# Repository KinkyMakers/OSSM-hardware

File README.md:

# OSSM - Open Source Sex Machine

**Maintained by [Research and Desire](https://researchanddesire.com), supported by the community.**

[Read the documentation here.](https://docs.researchanddesire.com/ossm)

## What is OSSM?

**OSSM** (pronounced like "awesome") is a user-friendly, open-source sex machine designed for everyday use. Whether you're curious about sex machines or looking to build your own, OSSM provides a powerful, customizable solution you can assemble at home.

OSSM uses a servo-powered belt-driven linear rail, enabling quiet operation, high torque, and software-defined stroke and depth control at speeds up to 1 meter per second.

### Performance Specifications

| Specification | Standard (20V DC) | High Power (36V DC) |
|---------------|-------------------|---------------------|
| Force output  | 32 lbs (14 kg)    | 50 lbs (22 kg)      |
| Stroke length | 8" (20 cm)        | 8" (20 cm)          |
| Rail size     | 350mm             | 350mm               |

### Why Build an OSSM?

- **Full control** over stroke length, depth, and speed through software
- **Quiet operation** suitable for shared living spaces
- **Customization options** through community-developed mods
- **Learning opportunities** in mechanics, electronics, and computing

## Quick Links

| Resource | Description |
|----------|-------------|
| [Documentation](https://docs.researchanddesire.com/ossm) | Complete build guides, hardware specs, and software reference |
| [R+D Store](https://researchanddesire.com) | Purchase motors, PCBs, wire harnesses, and complete kits |
| [KinkyMakers Discord](https://discord.gg/VtZcudpxT6) | Community discussion, build help, and mod development |
| [FAQs](https://docs.researchanddesire.com/ossm/guides/housekeeping/faqs) | Common questions about hardware, motors, printing, and control |

---

## Building Your OSSM

For complete step-by-step instructions, see the [Build Guide](https://docs.researchanddesire.com/ossm/guides/getting-started/build-guide/step-0.0_introduction).

### Bill of Materials

For the complete parts list with supplier links, see [Required Tools and Parts](https://docs.researchanddesire.com/ossm/guides/getting-started/build-guide/step-1.0_required_tools_and_parts).

### Electronics

| Component | Description | Documentation |
|-----------|-------------|---------------|
| Motor | 57AIM30 "Gold Motor" | [Motor Documentation](https://docs.researchanddesire.com/ossm/Hardware/motor/standard-build-motor) |
| Reference Board | OSSM PCB or ESP32 Development Board | [Board Design](https://docs.researchanddesire.com/ossm/Hardware/PCB/board-design) |
| Remote | OSSM Wired Remote | [Remote Documentation](https://docs.researchanddesire.com/ossm/Hardware/standard-printed-parts/remote/introduction) |
| Wiring | JST-PH 2.0 4-Pin data cable and 16awg power wire | [Wiring Guide](https://docs.researchanddesire.com/ossm/Hardware/motor/wiring-gold-motor) |

**Power Supply:** 20-36V DC (5.5 x 2.1 Barrel Plug). A 24V 5A supply is recommended. Higher voltage (up to 36V) provides increased force.

> **Portable Option:** USB Power Banks capable of true 100W USB PD generally work well.
> - INIU Power Bank P63-E1 100W (tested, works)
> - INIU B62 Power Bank 65W (tested, powers down on high load)

### Printed Parts

For 3D printing settings and material recommendations, see [3D Printing Parts](https://docs.researchanddesire.com/ossm/guides/getting-started/build-guide/step-1.2_3d-printing-parts).

| Assembly | Parts Included | Documentation |
|----------|----------------|---------------|
| [Actuator](Printed%20Parts/Actuator/) | Body, Belt Tensioner, Threaded End Effector | [Actuator Docs](https://docs.researchanddesire.com/ossm/Hardware/standard-printed-parts/actuator/introduction) |
| [Remote](Printed%20Parts/Remote/) | Body, Knobs, Top Cover | [Remote Docs](https://docs.researchanddesire.com/ossm/Hardware/standard-printed-parts/remote/introduction) |
| [Toy Mounting](Printed%20Parts/Toy%20Mounting/) | Flange Base, Vac-U-Lock Adapters | [Toy Mounting Docs](https://docs.researchanddesire.com/ossm/Hardware/standard-printed-parts/toy-mounting/introduction) |
| [Mounting](Printed%20Parts/Mounting/) | PitClamp Mini Ring/Base, PCB Enclosure | [Mounting Docs](https://docs.researchanddesire.com/ossm/Hardware/standard-printed-parts/pitclamp/README) |
| [Stand](Printed%20Parts/Stand/) | 3030 Extrusion Base Components | [Stand Docs](https://docs.researchanddesire.com/ossm/Hardware/standard-printed-parts/stand/introduction) |
| [Radiating PitClamp Stand](Printed%20Parts/OSSM%20Mods/Radiating%20PitClamp%20Stand/) | One- and two-arm kits with a captured handle and four-color artwork | [Kit files and notes](Printed%20Parts/OSSM%20Mods/Radiating%20PitClamp%20Stand/README.md) |

Experimental parts are developed in the [KinkyMakers Discord](https://discord.gg/wrENMKb3) `#ossm-print-testing` channel.

### Hardware Components

**GT2 Pulley**
- Qty 1: 8mm Bore, 20 Tooth, 10mm Width

**GT2 Timing Belt**
- Qty 1: 10mm Width, 500mm length

**MGN12H Rail + Bearing Block**
- Qty 1: Minimum 250mm, Suggested 350mm, Maximum 550mm
- Rail length = desired maximum stroke + 180mm
- Must be MGN**12H** (H = longer bearing block for stability, 12 = 12mm rail width)

**Ball Bearings**
- Qty 6: MR115-2RS 5x11x4mm

**Fasteners**
| Qty | Part |
|-----|------|
| 8 | M3x8 Socket Cap Head Bolt |
| 2 | M3x16 Socket Cap Head Bolt |
| 1 | M3x20 Socket Cap Head Bolt |
| 7 | M3 Hex Nut |
| 3 | M5x20 Socket Cap Head Bolt |
| 1 | M5 Hex Nut |
| 4 | M5x35 Socket Cap Head Bolt |
| 4 | M5 20mm Hex Coupling Nut (or M5 Hex Nut) |

Additional hardware is required for Stand, Mounting, and Remote assemblies. See the respective [Printed Parts](Printed%20Parts/) folders for details.

---

## Assembly

**Important:** The actuator rail direction is critical for pattern accuracy and safety. The proper orientation has the threaded end to the right when looking at the front face of the actuator body (the "M" side of the OSSM text on the cover).

Your rail should extend the threaded end first when booted. If this doesn't match your build's behavior, reverse your rail's printed hardware.

### Build Resources

| Resource | Description |
|----------|-------------|
| [Complete Build Guide](https://docs.researchanddesire.com/ossm/guides/getting-started/build-guide/step-0.0_introduction) | Step-by-step documentation with images |
| [OSSM Assembly Playlist](https://youtube.com/playlist?list=PLzSK7OAu3KNQsFo6WJGT8P28lfkD3xpps) | Video tutorials for each assembly step |
| [Complete Assembly - Follow Along Guide](https://www.youtube.com/watch?v=9lVobSEw_Uw) | Full 30-minute video walkthrough |

---

## Software

For firmware flashing and configuration, see the [Software Documentation](https://docs.researchanddesire.com/ossm/Software/getting-started/introduction).

| Resource | Description |
|----------|-------------|
| [Web Flasher](https://docs.researchanddesire.com/ossm/guides/getting-started/web-flasher) | Flash firmware directly from your browser |
| [PlatformIO Setup](https://docs.researchanddesire.com/ossm/Software/getting-started/PlatformIO) | Development environment for custom builds |
| [LED Status Guide](https://docs.researchanddesire.com/ossm/Software/getting-started/LED_Status) | Understanding indicator lights |
| [StrokeEngine](https://docs.researchanddesire.com/ossm/Software/motion/stroke-engine/introduction) | Motion control library documentation |
| [Hardware Tests](https://docs.researchanddesire.com/ossm/Software/getting-started/hardware-tests) | On-device test suites for verifying peripherals, BLE, WiFi, and homing |

---

## Getting Help

- [User Guide](https://docs.researchanddesire.com/ossm/guides/getting-started/user-guide/introduction) - Operating your OSSM
- [Troubleshooting](https://docs.researchanddesire.com/ossm/guides/getting-started/user-guide/troubleshooting) - Common issues and solutions
- [Safety Information](https://docs.researchanddesire.com/ossm/guides/housekeeping/safety/introduction) - Important safety guidance
- [Discord Community](https://discord.gg/VtZcudpxT6) - Real-time community support

---

## Contributing

OSSM is open-source hardware under the [CERN Open Hardware Licence Version 2 - Strongly Reciprocal](LICENSE).

- [How to Become a Contributor](https://docs.researchanddesire.com/ossm/guides/contributing/how-to-become-a-contributor)
- [Forking the Repository](https://docs.researchanddesire.com/ossm/guides/contributing/forking)
- [Reporting Issues](https://docs.researchanddesire.com/ossm/guides/contributing/reporting-issues)
- [Roadmap](https://docs.researchanddesire.com/ossm/guides/contributing/roadmap)

---

## About

- [About Research and Desire](https://docs.researchanddesire.com/ossm/guides/housekeeping/about-research-and-desire)
- [About Kinky Makers](https://docs.researchanddesire.com/ossm/guides/housekeeping/about-kinky-makers)
- [Open Source Certification](https://docs.researchanddesire.com/ossm/guides/housekeeping/open-source/introduction)

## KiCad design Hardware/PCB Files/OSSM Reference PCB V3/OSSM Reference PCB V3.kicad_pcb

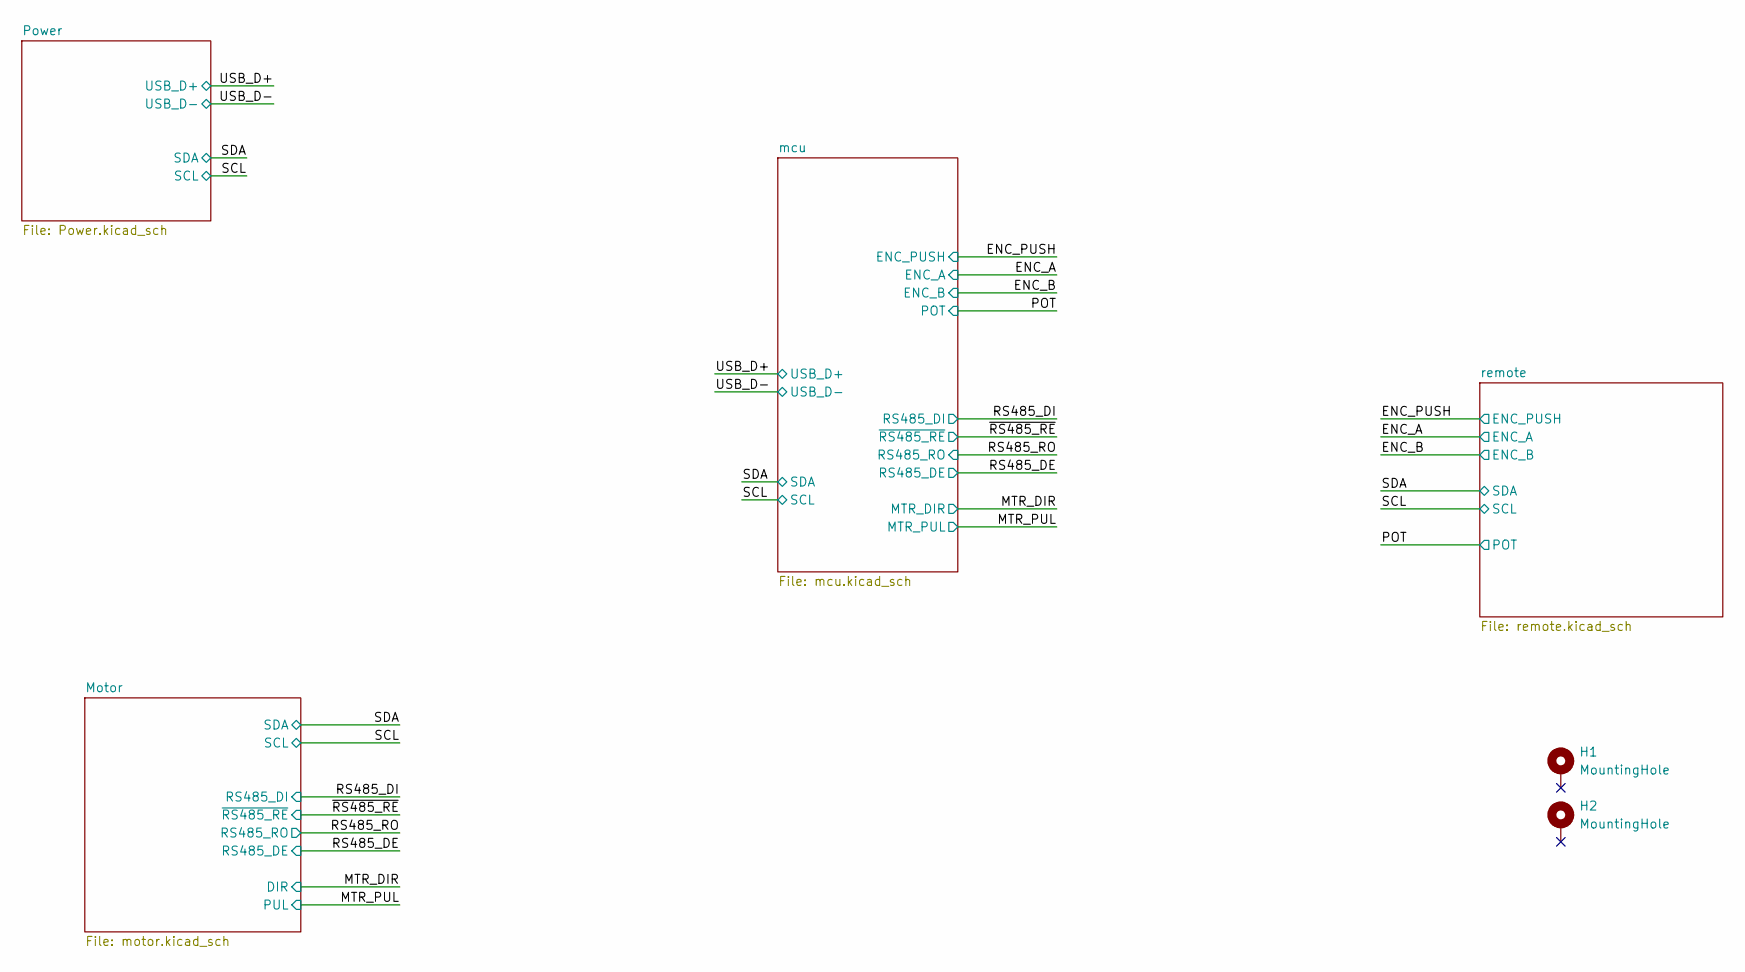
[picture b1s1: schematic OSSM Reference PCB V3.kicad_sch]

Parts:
H1, H2: MountingHole; MountingHole_4.3mm_M4_DIN965_Pad

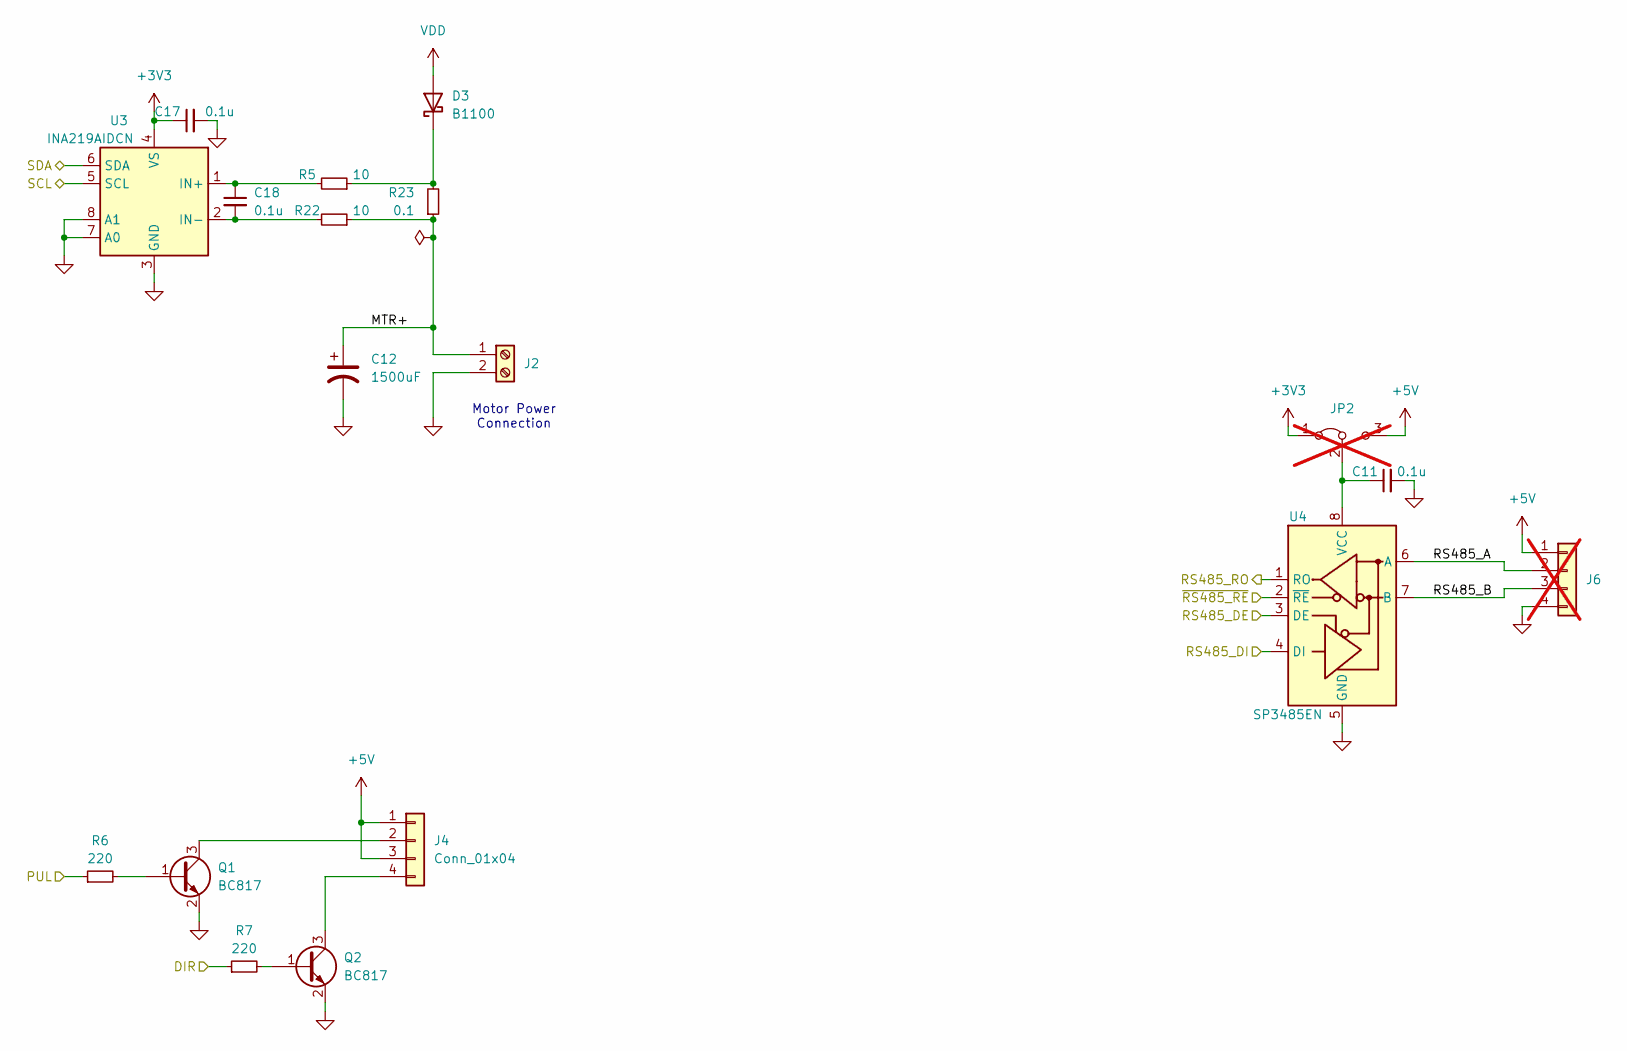
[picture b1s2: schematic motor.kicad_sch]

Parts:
C11: 0.1u; C_0402_1005Metric; MPN C77020
C12: 1500uF; CP_Radial_D12.5mm_P5.00mm_L25mm; MPN C2832301
C17, C18: 0.1u; C_0402_1005Metric; MPN C56392
D3: B1100; D_SMA; MPN C110106
J2: Screw_Terminal_01x02; TerminalBlock_Phoenix_MKDS-1,5-2_1x02_P5.00mm_Horizontal; MPN C8269
J4: Conn_01x04; Molex_Micro-Fit_3.0_43650-0400_1x04_P3.00mm_Horizontal
J6: Conn_01x04; PinSocket_1x04_P2.54mm_Vertical; not fitted
JP2: Jumper_3_Bridged12; SolderJumper-3_P1.3mm_Bridged12_Pad1.0x1.5mm; not fitted
Q1, Q2: BC817; SOT-23; MPN C52801
R5, R22: 10; R_0402_1005Metric
R6, R7: 220; R_0402_1005Metric
R23: 0.1; R_0603_1608Metric; MPN C111027
U3: INA219AIDCN; SOT-23-8; MPN C87469
U4: SP3485EN; SOIC-8_3.9x4.9mm_P1.27mm; MPN C8963

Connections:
+3V3: C17.1, JP2.1 (A), U3.4 (VS); also elsewhere on the board
+5V: J4.1, J4.3, J6.1, JP2.3 (B); also elsewhere on the board
/MTR_DIR: R7.1; also elsewhere on the board
/MTR_PUL: R6.1; also elsewhere on the board
/Motor/MTR+: C12.1, J2.1, R22.1, R23.1
/Motor/RS485_A: J6.2, U4.6 (A)
/Motor/RS485_B: J6.3, U4.7 (B)
/RS485_DE: U4.3 (DE); also elsewhere on the board
/RS485_DI: U4.4 (DI); also elsewhere on the board
/RS485_RO: U4.1 (RO); also elsewhere on the board
/SCL: U3.5 (SCL); also elsewhere on the board
/SDA: U3.6 (SDA); also elsewhere on the board
/~RS485_RE: U4.2 (~RE); also elsewhere on the board
GND: C11.2, C12.2, C17.2, J2.2, J6.4, Q1.2 (E), Q2.2 (E), U3.3 (GND), U3.7 (A0), U3.8 (A1), U4.5 (GND); also elsewhere on the board
unnamed: D3.1 (K), R5.1, R23.2
unnamed: J4.2, Q1.3 (C)
unnamed: J4.4, Q2.3 (C)
unnamed: C11.1, JP2.2 (C), U4.8 (VCC)
unnamed: Q1.1 (B), R6.2
unnamed: Q2.1 (B), R7.2
unnamed: C18.1, R5.2, U3.1 (IN+)
unnamed: C18.2, R22.2, U3.2 (IN-)
VDD: D3.2 (A); also elsewhere on the board

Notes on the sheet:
Motor Power Connection

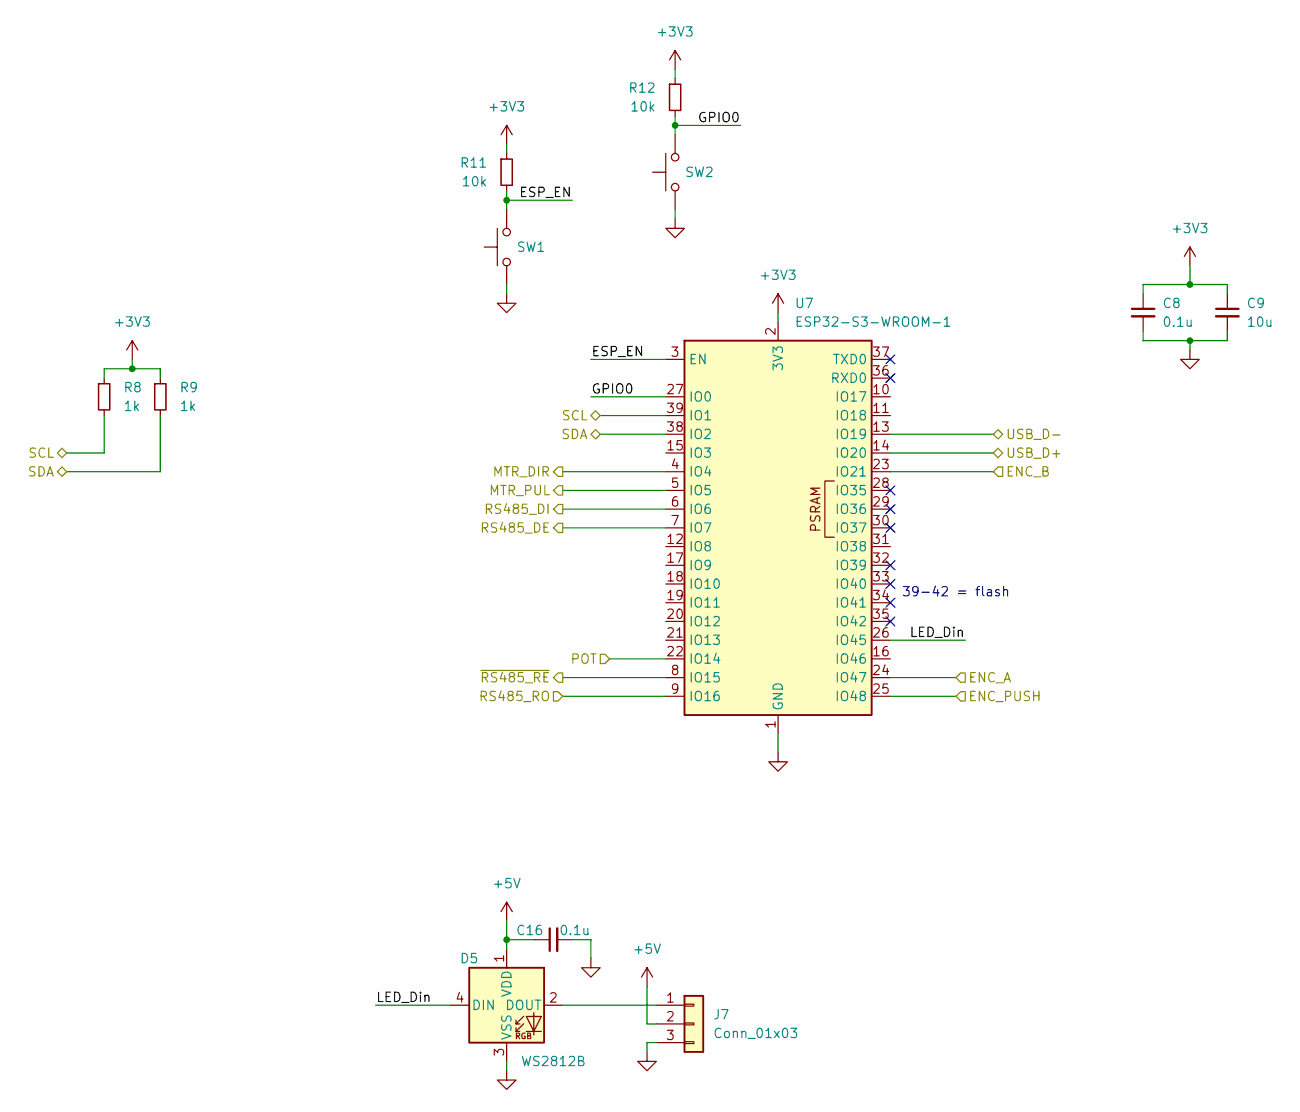
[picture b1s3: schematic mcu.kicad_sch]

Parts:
C8, C16: 0.1u; C_0402_1005Metric; MPN C77020
C9: 10u; C_0603_1608Metric; MPN C194427
D5: WS2812B; LED_WS2812B_PLCC4_5.0x5.0mm_P3.2mm; MPN C2843785
J7: Conn_01x03; PinHeader_1x03_P2.54mm_Vertical
R8, R9: 1k; R_0402_1005Metric
R11, R12: 10k; R_0402_1005Metric
SW1, SW2: SW_Push; SW_TACT_TS-1088-AR02016; MPN C720477
U7: ESP32-S3-WROOM-1; MPN C2913199

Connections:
+3V3: C8.1, C9.1, R8.1, R9.1, R11.1, R12.1, U7.2 (3V3); also elsewhere on the board
+5V: C16.1, D5.1 (VDD), J7.2; also elsewhere on the board
/ENC_A: U7.24 (IO47); also elsewhere on the board
/ENC_B: U7.23 (IO21); also elsewhere on the board
/ENC_PUSH: U7.25 (IO48); also elsewhere on the board
/MTR_DIR: U7.4 (IO4); also elsewhere on the board
/MTR_PUL: U7.5 (IO5); also elsewhere on the board
/POT: U7.22 (IO14); also elsewhere on the board
/RS485_DE: U7.7 (IO7); also elsewhere on the board
/RS485_DI: U7.6 (IO6); also elsewhere on the board
/RS485_RO: U7.9 (IO16); also elsewhere on the board
/SCL: R8.2, U7.39 (IO1); also elsewhere on the board
/SDA: R9.2, U7.38 (IO2); also elsewhere on the board
/USB_D+: U7.14 (IO20); also elsewhere on the board
/USB_D-: U7.13 (IO19); also elsewhere on the board
/mcu/ESP_EN: R11.2, SW1.2, U7.3 (EN)
/mcu/GPIO0: R12.2, SW2.2, U7.27 (IO0)
/mcu/LED_Din: D5.4 (DIN), U7.26 (IO45)
/~RS485_RE: U7.8 (IO15); also elsewhere on the board
GND: C8.2, C9.2, C16.2, D5.3 (VSS), J7.3, SW1.1, SW2.1, U7.1 (GND), U7.40 (GND), U7.41 (GND); also elsewhere on the board
unnamed: D5.2 (DOUT), J7.1

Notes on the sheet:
39-42 = flash

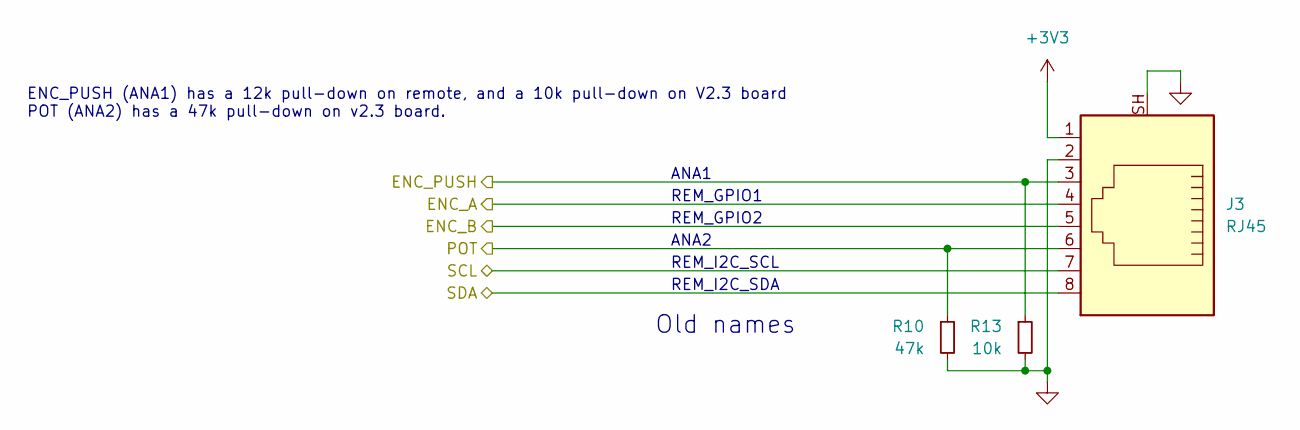
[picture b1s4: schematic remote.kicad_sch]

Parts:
J3: RJ45; RJ45_Connfly_DS1128-09-S8xx-S_Horizontal; MPN C86575
R10: 47k; R_0402_1005Metric
R13: 10k; R_0402_1005Metric

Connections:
+3V3: J3.1; also elsewhere on the board
/ENC_A: J3.4; also elsewhere on the board
/ENC_B: J3.5; also elsewhere on the board
/ENC_PUSH: J3.3, R13.1; also elsewhere on the board
/POT: J3.6, R10.1; also elsewhere on the board
/SCL: J3.7; also elsewhere on the board
/SDA: J3.8; also elsewhere on the board
GND: J3.2, J3.SH, R10.2, R13.2; also elsewhere on the board

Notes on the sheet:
ANA2
REM_I2C_SCL
REM_GPIO2
ANA1
ENC_PUSH (ANA1) has a 12k pull-down on remote, and a 10k pull-down on V2.3 board POT (ANA2) has a 47k pull-down on v2.3 board.
Old names
REM_I2C_SDA
REM_GPIO1

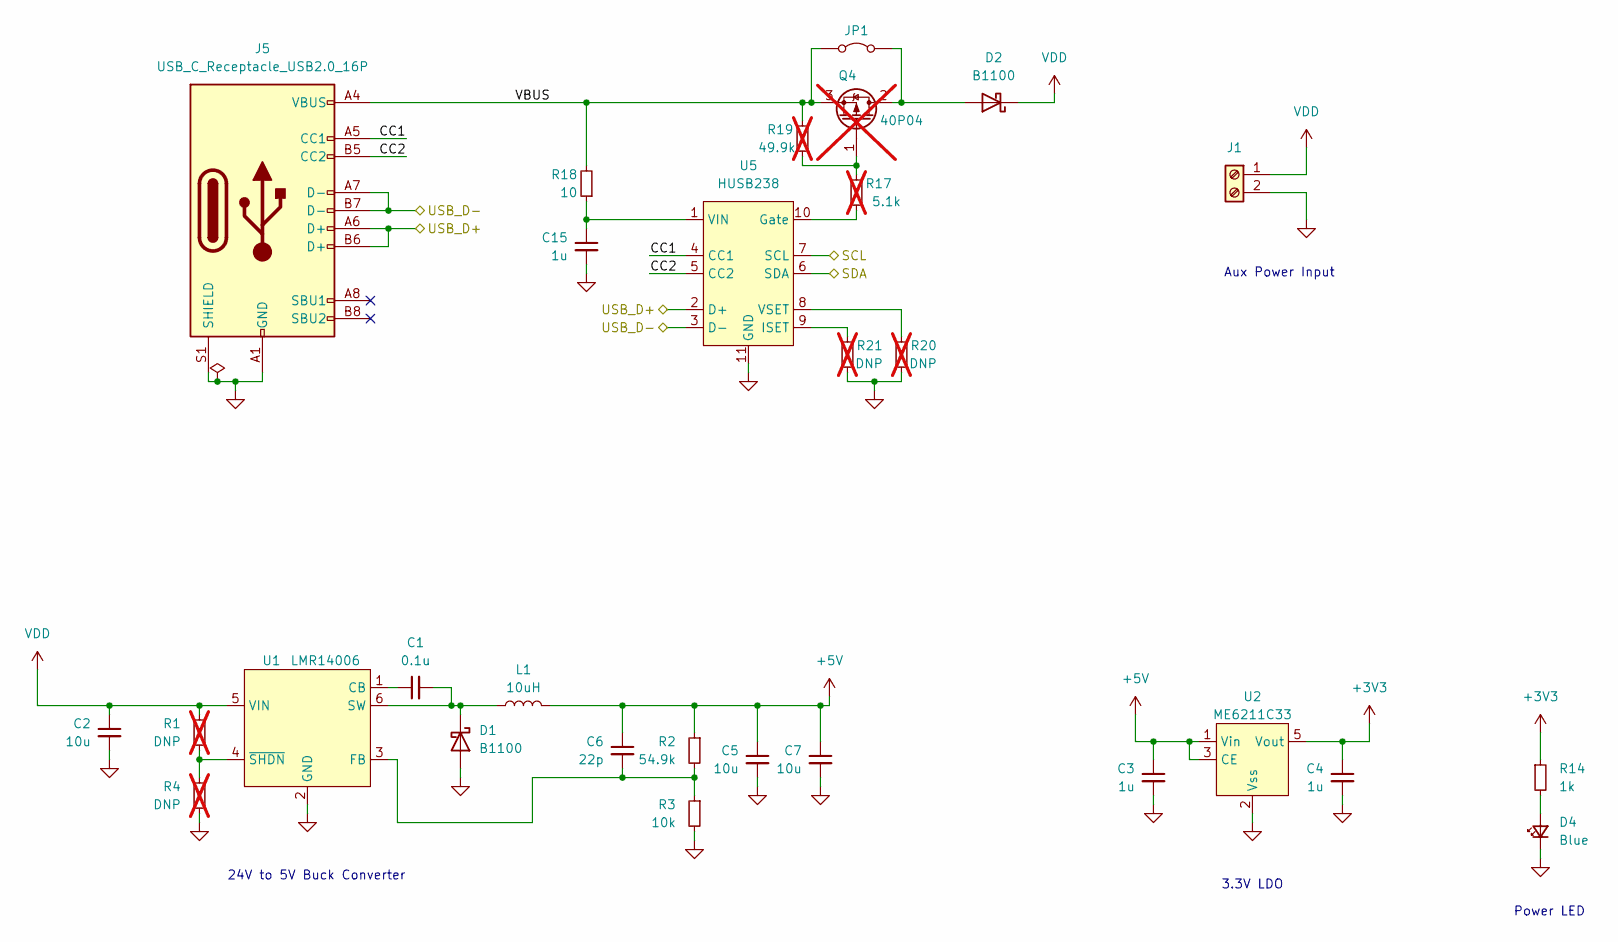
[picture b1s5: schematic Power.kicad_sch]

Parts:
C1: 0.1u; C_0402_1005Metric; MPN C77020
C2, C5, C7: 10u; C_0603_1608Metric; MPN C194427
C3, C4, C15: 1u; C_0402_1005Metric; MPN C1518208
C6: 22p; C_0402_1005Metric; MPN C76960
D1, D2: B1100; D_SMA; MPN C110106
D4: Blue; LED_0603_1608Metric; MPN C7496819
J1: Screw_Terminal_01x02; TerminalBlock_Phoenix_MKDS-1,5-2_1x02_P5.00mm_Horizontal; MPN C8269
J5: USB_C_Receptacle_USB2.0_16P; USB_C_Receptacle_HRO_TYPE-C-31-M-12; MPN C165948
JP1: Jumper_2_Bridged; SolderJumper-2_P1.3mm_Bridged_Pad1.0x1.5mm
L1: 10uH; L_Sunlord_SWPA4020S; MPN C98364
Q4: 40P04; TO-252-2; MPN C21882500; not fitted
R1, R4, R20, R21: DNP; R_0402_1005Metric; not fitted
R2: 54.9k; R_0402_1005Metric
R3: 10k; R_0402_1005Metric
R14: 1k; R_0402_1005Metric
R17: 5.1k; R_0402_1005Metric; MPN C278598; not fitted
R18: 10; R_0402_1005Metric
R19: 49.9k; R_0402_1005Metric; not fitted
U1: LMR14006; SOT-23-6; MPN C477919
U2: ME6211C33; SOT-23-5; MPN C82942
U5: HUSB238; DFN-10-1EP_3x3mm_P0.5mm_EP1.65x2.38mm_ThermalVias; MPN C7471904

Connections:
+3V3: C4.1, R14.1, U2.5 (Vout); also elsewhere on the board
+5V: C3.1, C5.1, C6.1, C7.1, L1.2, R2.1, U2.1 (Vin), U2.3 (CE); also elsewhere on the board
/Power/CC1: J5.A5 (CC1), U5.4 (CC1)
/Power/CC2: J5.B5 (CC2), U5.5 (CC2)
/Power/VBUS: J5.A4 (VBUS), J5.A9 (VBUS), J5.B4 (VBUS), J5.B9 (VBUS), JP1.1 (A), Q4.3 (S), R18.2, R19.2
/SCL: U5.7 (SCL); also elsewhere on the board
/SDA: U5.6 (SDA); also elsewhere on the board
/USB_D+: J5.A6 (D+), J5.B6 (D+), U5.2 (D+); also elsewhere on the board
/USB_D-: J5.A7 (D-), J5.B7 (D-), U5.3 (D-); also elsewhere on the board
GND: C2.2, C3.2, C4.2, C5.2, C7.2, C15.2, D1.2 (A), D4.1 (K), J1.2, J5.A1 (GND), J5.A12 (GND), J5.B1 (GND), J5.B12 (GND), J5.S1 (SHIELD), R3.2, R4.2, R20.1, R21.1, U1.2 (GND), U2.2 (Vss), U5.11 (GND); also elsewhere on the board
unnamed: C1.2, D1.1 (K), L1.1, U1.6 (SW)
unnamed: D2.2 (A), JP1.2 (B), Q4.2 (D)
unnamed: D4.2 (A), R14.2
unnamed: Q4.1 (G), R17.2, R19.1
unnamed: C1.1, U1.1 (CB)
unnamed: C6.2, R2.2, R3.1, U1.3 (FB)
unnamed: R1.2, R4.1, U1.4 (~SHDN)
unnamed: R17.1, U5.10 (Gate)
unnamed: R21.2, U5.9 (ISET)
unnamed: C15.1, R18.1, U5.1 (VIN)
unnamed: R20.2, U5.8 (VSET)
VDD: C2.1, D2.1 (K), J1.1, R1.1, U1.5 (VIN); also elsewhere on the board

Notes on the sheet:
Power LED
Aux Power Input
3.3V LDO
24V to 5V Buck Converter

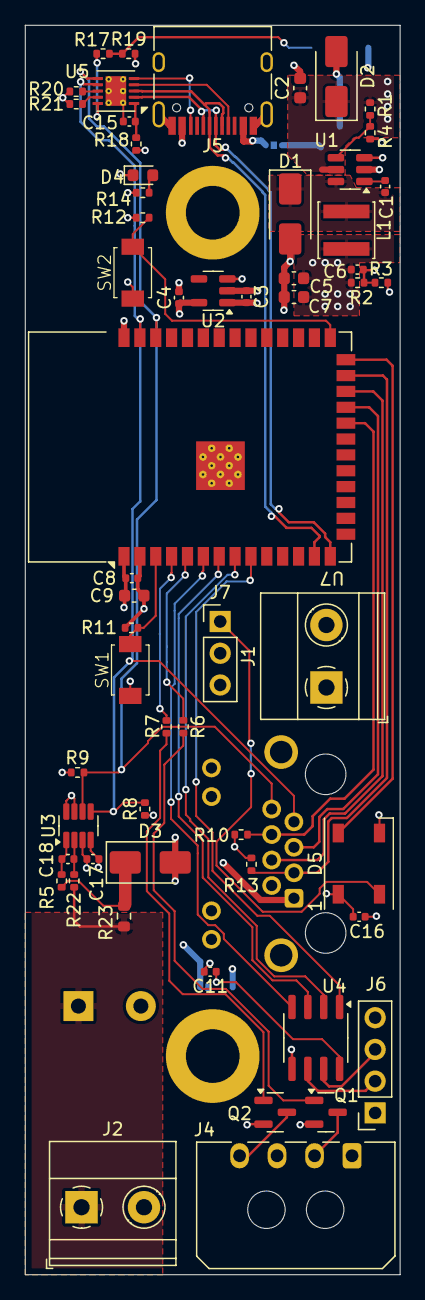
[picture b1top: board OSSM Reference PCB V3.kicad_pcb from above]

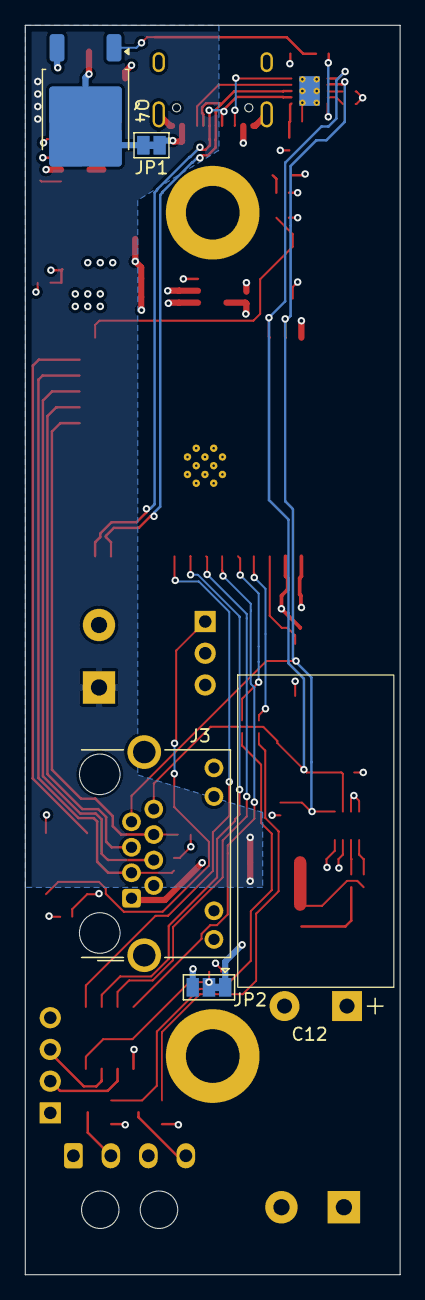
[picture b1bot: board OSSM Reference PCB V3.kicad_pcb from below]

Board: 4 copper layers, 30.0 x 100.0 mm, 64 parts (5 on the bottom side), 47 nets.

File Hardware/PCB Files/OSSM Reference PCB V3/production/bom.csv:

Designator,Footprint,Quantity,Value,LCSC Part #
"C1, C11, C16, C17, C18, C8",0402,6,0.1u,C56392
C12,CP_Radial_D12.5mm_P5.00mm_L25mm,1,1500uF,C2832301
"C15, C3, C4",0402,3,1u,C1518208
"C2, C5, C7, C9",0603,4,10u,C194427
C6,0402,1,22p,C76960
"D1, D2, D3",D_SMA,3,B1100,C110106
D4,0603,1,Blue,C7496819
D5,LED_WS2812B_PLCC4_5.0x5.0mm_P3.2mm,1,WS2812B,C2843785
"J1, J2","TerminalBlock_Phoenix_MKDS-1,5-2_1x02_P5.00mm_Horizontal",2,Screw_Terminal_01x02,C8269
J3,RJ45_Connfly_DS1128-09-S8xx-S_Horizontal,1,RJ45,C86575
J5,USB_C_Receptacle_HRO_TYPE-C-31-M-12,1,USB_C_Receptacle_USB2.0_16P,C165948
L1,L_Sunlord_SWPA4020S,1,10uH,C98364
"Q1, Q2",SOT-23,2,BC817,C52801
R10,0402,1,47k,C25792
"R11, R12, R13, R3",0402,4,10k,C60490
"R14, R8, R9",0402,3,1k,C11702
"R18, R22, R5",0402,3,10,C25077
R2,0402,1,54.9k,C5126159
R23,0603,1,0.1,C111027
"R6, R7",0402,2,220,C112291
"SW1, SW2",SW_TACT_TS-1088-AR02016,2,SW_Push,C720477
U1,SOT-23-6,1,LMR14006,C477919
U2,SOT-23-5,1,ME6211C33,C82942
U3,SOT-23-8,1,INA219AIDCN,C87469
U4,SOIC-8_3.9x4.9mm_P1.27mm,1,SP3485EN,C8963
U5,DFN-10-1EP_3x3mm_P0.5mm_EP1.65x2.38mm_ThermalVias,1,HUSB238,C7471904
U7,ESP32-S3-WROOM-1,1,ESP32-S3-WROOM-1,C2913199

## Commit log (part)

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2026-02-24 Temporary patch
2026-02-24 docs: sync ossm documentation from docs repo
2026-02-25 Go to point pattern for stroke engine.
2026-02-25 Same issue... any motion is spamming nimble updates to connected devices.
2026-02-25 Add detail to MQTT payload
2026-02-25 Consolidated streaming code updates
2026-02-25 Better default buffer
2026-02-27 Reset queue when launching streaming mode
2026-02-28 Faster homing, with userconfig for where the device should park afterwards.
2026-03-01 4x Current, but 4x faster
2026-03-02 Fix MQTT local sync
2026-03-02 Fix - does connect
2026-03-02 Fix and fingerprint
2026-03-02 Unneeded movement with new homing code
2026-03-02 Latency Characteristic
2026-03-03 docs: migrate SaladDressing mod content to documentation site
    - Add motor-cover.mdx and dp-attachment.mdx pages with hero images
    - Enrich capstan.mdx with MGN12H vs HG20 comparison, tabbed BOMs,
    inline fastener lists, assembly guide links, and full CAD file links
    - Add "Printed parts and CAD files" sections with GitHub links to all
    STEP/3MF/STL files across suction-cup-bracket, weight-plate, and
    quick-change-toy-mount pages
2026-03-03 docs: migrate legacy JPGs to webp and remove source Pictures/ directories
    - Convert additional detail/angle photos to webp and co-locate in docs _images/
    - dp-attachment-top.webp (bracket top-down view)
    - motor-cover-rear.webp, motor-cover-back.webp (heatsink angles)
    - capstan-hg20-front.webp, capstan-hg20-side.webp (HG20 overview shots)
    - Add new images to motor-cover, dp-attachment, and capstan MDX pages
    - Delete all 54 legacy JPGs from Printed Parts Pictures/ directories
2026-03-03 fix imports
2026-03-03 restore mermaid controls
2026-03-03 Simplify Docs and add MakerWorld Links
2026-03-03 Restore some material tips
2026-03-03 Remove react import
2026-03-03 Characteristic doc
2026-03-04 Basic CSV support
2026-03-04 spacing
2026-03-06 WIP commit
2026-03-09 documentation and critical bug fix
2026-03-09 removed power saving since the OSSM does not run on battery and it was causing the OSSM setup connection to fail
2026-03-09 --no-docs Simple bug fix, no UI changes
2026-03-09 String compare
2026-03-10 Display Tests
2026-03-10 Add display documentation section with UI library docs
    Move display service docs to a dedicated Display section and add
    documentation for the lib/ui rendering library covering TextPages,
    strings, icons, logos, and visual test infrastructure.
    Made-with: Cursor
2026-03-10 temp
2026-03-10 AUTO: Version bump 1.0.12
2026-03-10 Added is-paired polling to the backend so that the screen confirms the successful pairing after the user enters the pairing code on the UI
2026-03-11 AUTO: Version bump 1.0.13
2026-03-11 AUTO: Version bump 1.0.14
2026-03-11 RAD-1957
2026-03-11 Fix MQTT connection and icons
2026-03-11 shortened the URL to make the qr code work (less characters)
2026-03-11 fix icons
2026-03-11 Added pairing loading screen so the UI doesn't seem to freeze
2026-03-11 Added return text + consolidated all the pages to TextPages file (minor refactor)
2026-03-11 payload tests
2026-03-11 Commented out the polling code
2026-03-11 AUTO: Version bump 1.0.15
2026-03-14 Pattern page fix
2026-03-14 Fix and move link
2026-03-16 Reverse setting bug fix
2026-03-16 AUTO: Version bump 1.0.16
2026-03-16 Buffer state and loop
2026-03-16 Not depth
2026-03-20 initial hw test setup
2026-03-23 UPdated the tests to reuse code and not write it's own hardware control functions
2026-03-23 Updated the platformio.ini file to enable the newly added tests
2026-03-23 Undoing wronfgul update to the .ini file
2026-03-23 Added developer documentation
2026-03-23 Minor update to the readme.md to link to the new test pae
2026-03-23 Add go:restart and go:update BLE commands to OSSM firmware
2026-03-23 Fix hardware test homing slamming into hard stops by suppressing verbose GPIO logs
    Without esp_log_level_set(gpio, ESP_LOG_WARN), the ESP-IDF GPIO/ADC
    drivers emit debug logs on every analogRead() call during the homing
    current-sensing loop. Each log blocks on Serial output, starving the
    loop and delaying stall detection — causing the motor to grind against
    the hard stops for hundreds of milliseconds before stopping.
    Production (main.cpp) already suppresses these logs. Adding the same
2026-03-24 AUTO: Version bump 1.0.17
2026-03-24 AUTO: Version bump 1.0.18
2026-03-24 ALl unit tests now pass
2026-03-25 AUTO: Version bump 1.0.19
2026-03-25 Phase 2 cont.: updating simple penetration to work with the radr
2026-03-26 Phase 3.2.0: Aded eFuse MAX hex fielf to BLE pairing charactarestic value, backward-compatible
2026-03-30 Undoing accidental git commit
2026-03-30 AUTO: Version bump 1.0.20
2026-03-30 Remove build artifacts and broken submodule from main
    Removes files that were accidentally included in PR #262:
    - Software/components/esp_littlefs (submodule ref with no .gitmodules)
    - Software/dependencies.lock
    - Software/sdkconfig.development
    - Reverts compile_commands.json to pre-merge state
    The esp_littlefs submodule reference was causing CI checkout failures.
2026-03-30 AUTO: Version bump 1.0.21
2026-03-30 Release workflow
2026-03-30 AUTO: Version bump 1.0.22
2026-03-30 AUTO: Version bump 1.0.23
2026-04-01 AUTO: Version bump 1.0.24
2026-04-02 Added Picatinny Rail Mod under /Printed Parts/OSSM Mods/LaikaTheHuskie's Mods
2026-04-04 Early draft of pattern control
2026-04-08 Create OSSM Universal Toy Mounting
    Universal Mounting structure for mounting toys to the OSSM
2026-04-09 Uploaded Work in progress mounting plates and attachments
2026-04-09 Added New Plates,
2026-04-11 Added some hardware, removed some redundant parts
2026-04-11 added gridfinity nut and bolt holders
2026-04-11 Fixed some errors in plates and added missing holes in in a backplate that was missing it
2026-04-13 multiplate WIP added
2026-04-19 Before installing library
2026-04-19 Ok.. we're using spline.h
2026-04-26 Before trying acceleration control
2026-04-27 feat(funscript-player): add built-in example funscript loader (RAD-1897)
    Adds a button under the funscript file picker that loads a short, built-in
    example funscript (slow -> medium -> fast strokes) so new users can test
    the player and verify their OSSM is responding correctly without first
    needing to source a script from elsewhere.
    Linear: https://linear.app/researchanddesire/issue/RAD-1897
2026-04-27 fix(funscript-player): address RAD-2053 safety + UX issues
    Improve the OSSM funscript player to fix three of the four problems
    reported in RAD-2053:
    1. Android video picker (Issue 1): drop accept="video/*" so the
    system picker opens the full file browser instead of forcing the
    user into the Photos / Gallery app, which hid files on network
    drives.
2026-04-28 fix(funscript-player): hold reverse/simple in refs to defeat stale closure (RAD-1993)
    The Funscript Player runs a setInterval at 2ms that captured a stale
    React closure of `syncFunscript`. After toggling Reverse (or rapid
    play/pause around it), the running interval could keep emitting
    non-reversed positions for ~1-2 seconds before "fixing itself".
    This switches `isReverse` and `isSimple` to ref-mirrored values so
    each sync tick reads the current toggle. The setInterval is also
2026-04-29 Feature to rename OSSM
2026-04-29 Shorter name
2026-04-30 8 Characters
2026-04-30 Even better homing
2026-04-30 Double tap all instrokes
2026-04-30 Only bump twice if stroke is short
2026-04-30 Pin to 2.4 as 2.5 is currently incompatible
2026-04-30 Incorrect test result
2026-05-01 Check in case of mid session stiction
2026-05-03 Before reviewing public PRS
2026-05-03 Reboot after rename
2026-05-05 Add state characteristic read callback for live positionMm
    The state characteristic's notify path only fires when the fingerprint
    changes (settings, state-machine state, pattern, sessionId). The
    fingerprint excludes positionMm, so a remote BLE client that polls via
    readValue() gets stale position data between settings changes — the
    characteristic buffer is only updated when the fingerprint changes.
    This callback runs getCurrentState() on each read so polling clients
2026-05-11 AUTO: Version bump 1.0.25
2026-05-17 Bump axios from 1.10.0 to 1.13.2 in /Documentation
    Bumps [axios](https://github.com/axios/axios) from 1.10.0 to 1.13.2.
    - [Release notes](https://github.com/axios/axios/releases)
    - [Changelog](https://github.com/axios/axios/blob/v1.x/CHANGELOG.md)
    - [Commits](https://github.com/axios/axios/compare/v1.10.0...v1.13.2)
    ---
    updated-dependencies:
2026-05-23 clean up
2026-05-23 AUTO: Version bump 1.0.26
2026-05-23 remove supabase
2026-05-23 AUTO: Version bump 1.0.27
2026-05-23 master deploy fix
2026-05-23 AUTO: Version bump 1.0.28
2026-05-25 build: bank stale local build-config (19d stale, no competing path)
    - platformio.ini: silence int-in-bool-context errors, pin espressif32@6.3.2
    - sdkconfig.development: regenerated to current ESP-IDF defaults
    - dependencies.lock: idf 4.4.4 (target esp32)
    Banked per CLAUDE.md stale-WIP-as-canonical rule (file mtime 19d, no
    upstream commits touched these paths since).
2026-05-28 for review, still choppy
2026-06-03 dev, no stepper
2026-06-04 fix streaming zero division
2026-06-14 Add direction change characteristic and user config service
2026-06-14 Fixes mid-rail logic. Aligns with other modes
2026-06-14 Test fixes
2026-06-16 Make not homed part of emergency stop, and standardize on that behavior when leaving a mode
2026-06-17 --no-docs fixing ota, should be invisible to users
2026-06-17 AUTO: Version bump 1.0.29
2026-06-18 AUTO: Version bump 1.0.30
2026-06-18 AUTO: Version bump 1.0.31
